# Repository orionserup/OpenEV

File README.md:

# OpenEV

A completely open source project designing electric vehicles from scratch.

All PCBs are made in [KiCad](https://www.kicad.org/) Version 6.0

All 3D Models are generated in [FreeCAD](https://www.freecadweb.org/) Version 0.19.1

All Firmware written in C using the [ESP-IDF](https://www.espressif.com/en/products/sdks/esp-idf) Framework

All Microcontrollers are using the Open Source [RISC-V](https://riscv.org/) Architecture: [ESP32-C3](https://www.espressif.com/en/products/socs/esp32-c3)

## Branches

* Sk8: Configuration for an Electric Skateboard
* Scoot: Configuration for Electric Scooters and Bikes

## Documentation

For each component there is a Documentation folder. For the Firmware components there are both PDF and HTML reference manuals. For the Hardware and Model Components there are PDF Data and Reference Sheets

## Authors

[Orion Serup](orionserup@gmail.com)

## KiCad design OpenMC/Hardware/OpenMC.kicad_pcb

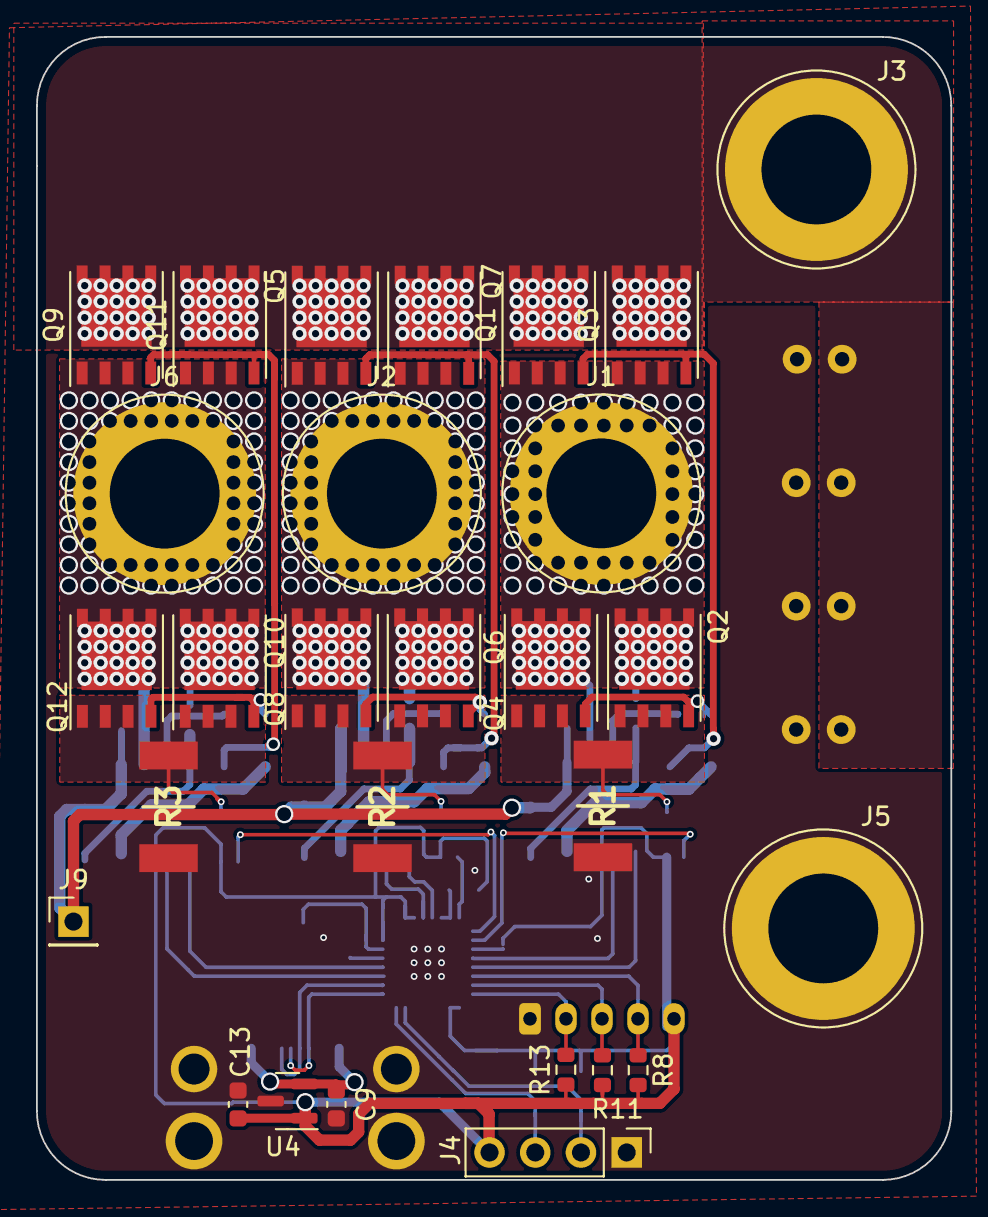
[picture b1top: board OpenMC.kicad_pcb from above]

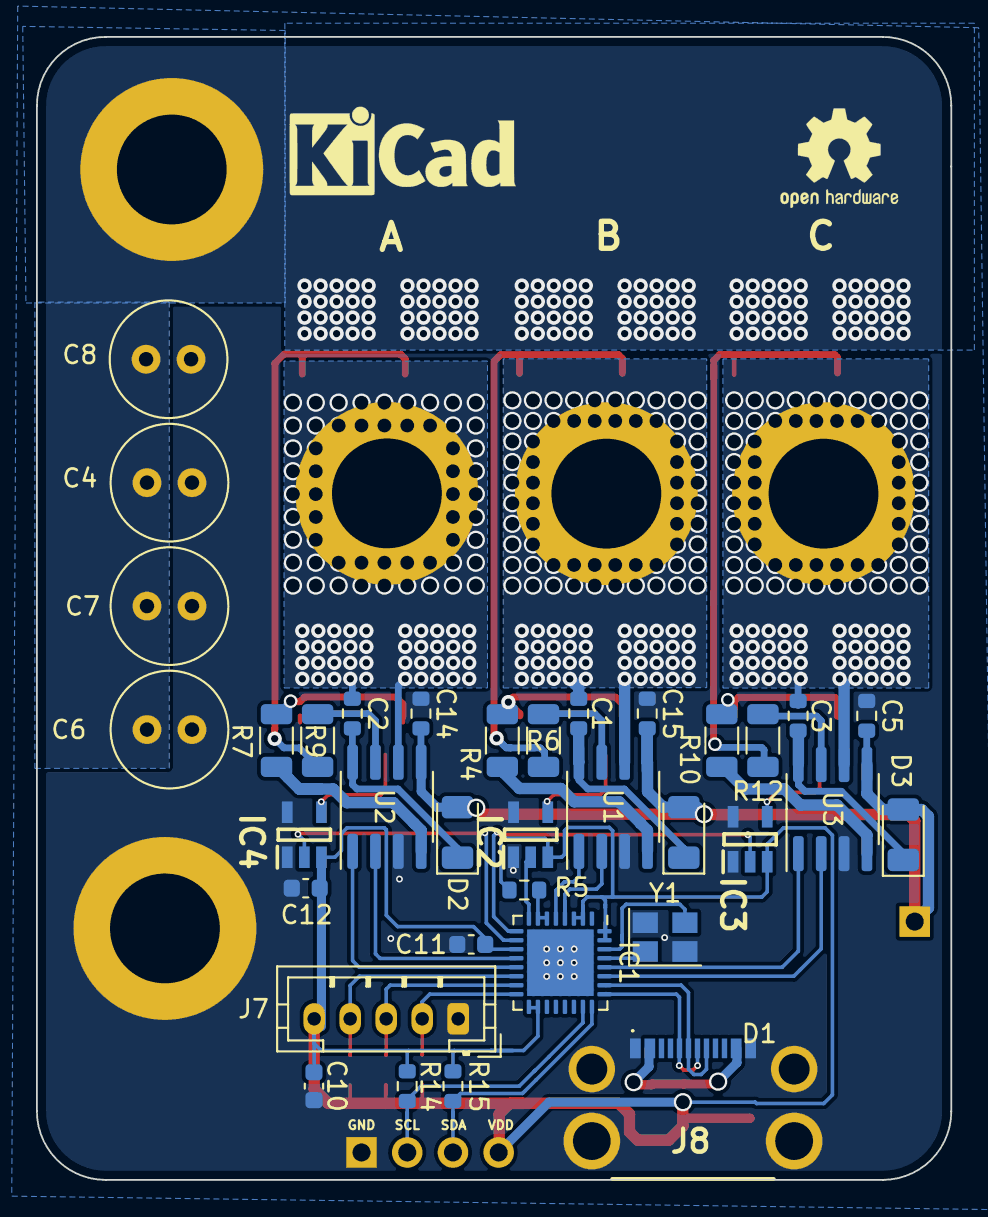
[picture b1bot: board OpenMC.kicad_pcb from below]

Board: 2 copper layers, 50.8 x 63.5 mm, 63 parts (35 on the bottom side), 45 nets.

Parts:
C1, C2, C3, C5, C14, C15: 1uF; R_0603_1608Metric
C4, C6, C7, C8: 27uF; C_Radial_D6.3mm_H7.0mm_P2.50mm
C9, C10, C11, C12, C13: 1uF; C_0603_1608Metric
D1, D2, D3: D; D_1206_3216Metric
IC1: ESP32-C3; QFN-32-1EP_5x5mm_P0.5mm_EP3.7x3.7mm
IC2, IC3, IC4: INA186A4QDBVRQ1; SOT95P280X145-5N
J1, J2, J6: Conn_01x01_Female; Banana_Jack_1Pin
J3: Power+; Banana_Jack_1Pin
J4: Comm; PinHeader_1x04_P2.54mm_Vertical
J5: Power-; Banana_Jack_1Pin
J7: Hall Connector; JST_PH_B5B-PH-K_1x05_P2.00mm_Vertical
J8: 216990-0001; 2169900001
J9: Gate Drive Voltage; PinHeader_1x01_P2.54mm_Vertical
Q1, Q2, Q3, Q4, Q5, Q6, Q7, Q8, Q9, Q10, Q11, Q12: SIR188DP; PowerPAK_SO-8_Single
R1, R2, R3: WSLF25121L000FEB; RESC6430X38N
R4, R6, R7, R9, R10, R12: 10; R_1206_3216Metric
R5, R8, R11, R13, R14, R15: R_US; R_0603_1608Metric
U1, U2, U3: LT2190NTR; SOIC-8_3.9x4.9mm_P1.27mm
U4: LM3480-3.3; SOT-23
Y1: 40MHz; Crystal_SMD_SeikoEpson_TSX3225-4Pin_3.2x2.5mm

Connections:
+BATT: C4.1, C6.1, C7.1, C8.1, J3.1, Q1.5 (D), Q3.5 (D), Q5.5 (D), Q7.5 (D), Q9.5 (D), Q11.5 (D)
/A: C2.2, J1.1, Q1.1 (S), Q1.2 (S), Q1.3 (S), Q2.5 (D), Q3.1 (S), Q3.2 (S), Q3.3 (S), Q4.5 (D), U2.6 (V_{s})
/B: C1.2, J2.1, Q5.1 (S), Q5.2 (S), Q5.3 (S), Q6.5 (D), Q7.1 (S), Q7.2 (S), Q7.3 (S), Q8.5 (D), U1.6 (V_{s})
/C: C3.2, J6.1, Q9.1 (S), Q9.2 (S), Q9.3 (S), Q10.5 (D), Q11.1 (S), Q11.2 (S), Q11.3 (S), Q12.5 (D), U3.6 (V_{s})
/Controller/AH: IC1.13 (MTDO), U2.1 (H_{in})
/Controller/AL: IC1.12 (MTCK), U2.2 (L_{in})
/Controller/BH: IC1.5 (XTAL_32K_N), U1.1 (H_{in})
/Controller/BL: IC1.4 (XTAL_32K_P), U1.2 (L_{in})
/Controller/CH: IC1.28 (U0TXD), U3.1 (H_{in})
/Controller/CL: IC1.27 (U0RXD), U3.2 (L_{in})
/Controller/D+: IC1.26 (GPIO19), J8.A6 (DP1), J8.B6 (DP2)
/Controller/D-: IC1.25 (GPIO18), J8.A7 (DN1), J8.B7 (DN2)
/Controller/HALL_A: IC1.16 (GPIO10), J7.2, R13.2
/Controller/HALL_B: IC1.15 (GPIO9), J7.3, R11.2
/Controller/HALL_C: IC1.14 (GPIO8), J7.4, R8.2
/Controller/I_{SENSE}A: IC1.10 (MTDI), IC4.2 (OUT)
/Controller/I_{SENSE}B: IC1.8 (GPIO3), IC2.2 (OUT)
/Controller/I_{SENSE}C: IC1.9 (MTMS), IC3.2 (OUT)
/Controller/RST: IC1.6 (GPIO2), IC1.7 (CHIP_EN), R5.2
/Controller/SCL: IC1.23 (SPID), J4.2, R14.2
/Controller/SDA: IC1.24 (SPIQ), J4.3, R15.2
/Controller/VBUS: C9.1, J8.A4 (VBUS_1), J8.A9 (VBUS_2), J8.B4 (VBUS_3), J8.B9 (VBUS_4), U4.2 (VI)
/Driver FETs/AH: Q1.4 (G), Q3.4 (G), R9.2
/Driver FETs/AL: Q2.4 (G), Q4.4 (G), R7.1
/Driver FETs/BH: Q5.4 (G), Q7.4 (G), R6.2
/Driver FETs/BL: Q6.4 (G), Q8.4 (G), R4.1
/Driver FETs/CH: Q9.4 (G), Q11.4 (G), R12.2
/Driver FETs/CL: Q10.4 (G), Q12.4 (G), R10.1
/Driver FETs/ISA: IC4.4 (IN-), Q2.1 (S), Q2.2 (S), Q2.3 (S), Q4.1 (S), Q4.2 (S), Q4.3 (S), R1.2
/Driver FETs/ISB: IC2.4 (IN-), Q6.1 (S), Q6.2 (S), Q6.3 (S), Q8.1 (S), Q8.2 (S), Q8.3 (S), R2.2
/Driver FETs/ISC: IC3.4 (IN-), Q10.1 (S), Q10.2 (S), Q10.3 (S), Q12.1 (S), Q12.2 (S), Q12.3 (S), R3.2
/Pre-Driver/V_{DRIVE}: C5.1, C14.1, C15.1, D1.2 (A), D2.2 (A), D3.2 (A), J9.1, U1.5 (V_{cc}), U2.5 (V_{cc}), U3.5 (V_{cc})
/VDD: C10.1, C11.1, C12.1, C13.1, IC1.2 (VDD3P3_1), IC1.3 (VDD3P3_2), IC1.11 (VDD3P3_RTC), IC1.17 (VDD3P3_CPU), IC1.18 (VDD_SPI), IC1.31 (VDDA_1), IC1.32 (VDDA_2), IC2.3 (VS), IC3.3 (VS), IC4.3 (VS), J4.4, J7.5, R5.1, R8.1, R11.1, R13.1, R14.1, R15.1, U4.1 (VO)
Earth: C4.2, C5.2, C6.2, C7.2, C8.2, C9.2, C10.2, C11.2, C12.2, C13.2, C14.2, C15.2, IC1.33 (GND), IC2.1 (GND), IC2.5 (IN+), IC3.1 (GND), IC3.5 (IN+), IC4.1 (GND), IC4.5 (IN+), J4.1, J5.1, J7.1, J8.A1 (GND_1), J8.A12 (GND_2), J8.B1 (GND_3), J8.B12 (GND_4), J8.MH1, J8.MH2, J8.MH3, J8.MH4, R1.1, R2.1, R3.1, U1.3 (GND), U2.3 (GND), U3.3 (GND), U4.3 (GND), Y1.2, Y1.4
unnamed: C1.1, D1.1 (K), U1.8 (V_{B})
unnamed: C2.1, D2.1 (K), U2.8 (V_{B})
unnamed: C3.1, D3.1 (K), U3.8 (V_{B})
unnamed: IC1.29 (XTAL_N), Y1.1
unnamed: IC1.30 (XTAL_P), Y1.3
unnamed: R4.2, U1.4 (L_{out})
unnamed: R6.1, U1.7 (H_{out})
unnamed: R7.2, U2.4 (L_{out})
unnamed: R9.1, U2.7 (H_{out})
unnamed: R10.2, U3.4 (L_{out})
unnamed: R12.1, U3.7 (H_{out})

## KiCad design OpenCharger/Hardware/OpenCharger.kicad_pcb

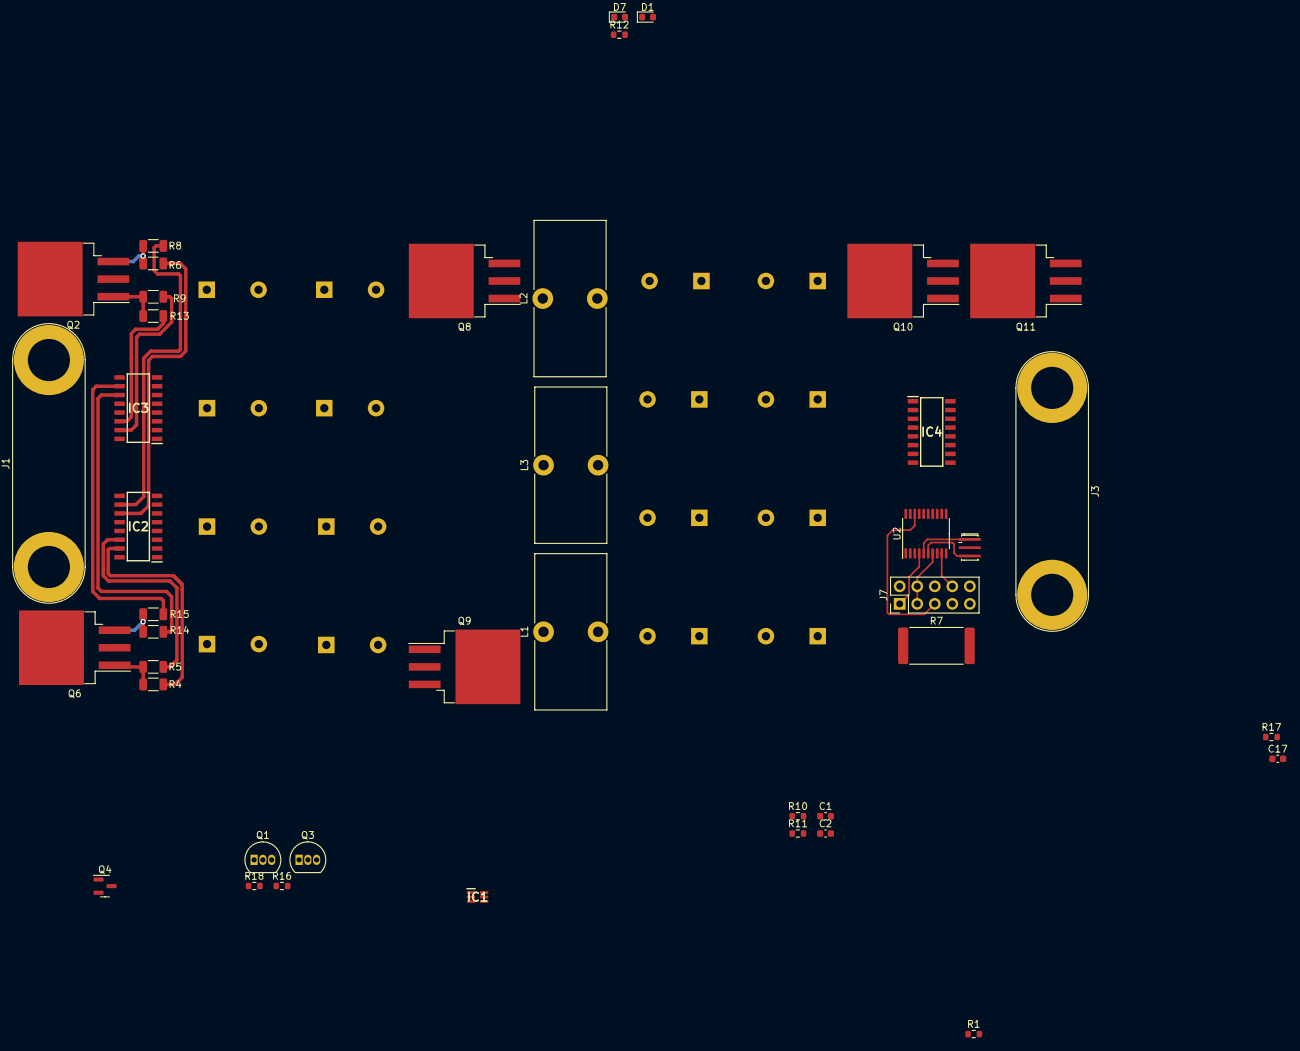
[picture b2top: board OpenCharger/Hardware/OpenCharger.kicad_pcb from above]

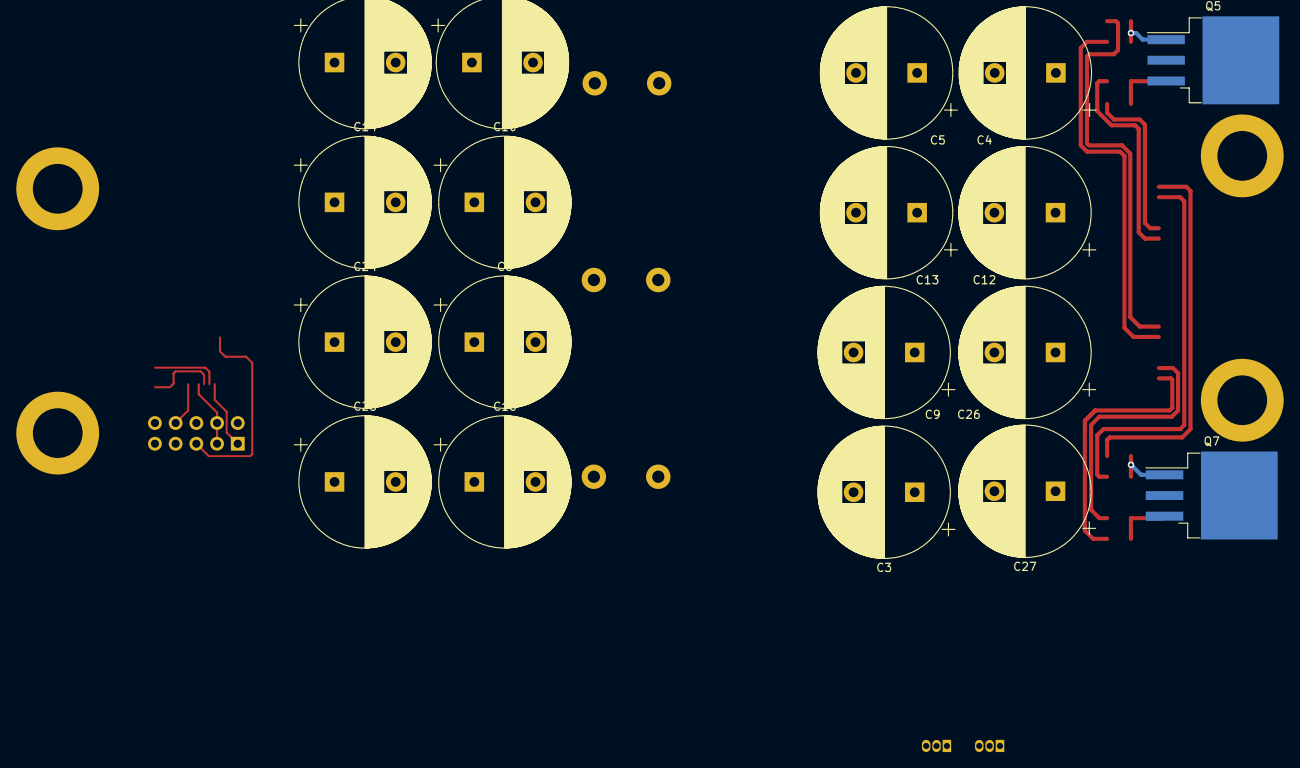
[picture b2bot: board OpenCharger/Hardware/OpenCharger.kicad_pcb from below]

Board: 2 copper layers, 60 parts (18 on the bottom side), 37 nets.

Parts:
C1, C2, C17: C; C_0603_1608Metric
C3, C4, C5, C6, C8, C9, C10, C12, C13, C14, C15, C16, C24, C25, C26, C27: 100uF; CP_Radial_D16.0mm_P7.50mm
D1, D7: 5V; D_0603_1608Metric
IC1: INA211CQDCKRQ1; SOT65P210X110-6N
IC2, IC3, IC4: STDRIVEG600TR; SOIC127P600X175-16N
J1, J3: Conn_01x02; Banana_Jack_2Pin
J7: Conn_02x05_Odd_Even; PinHeader_2x05_P2.54mm_Vertical
L1, L2, L3: L; L_Toroid_Vertical_L22.4mm_W10.2mm_P7.90mm_Vishay_TJ4
Q1, Q3: BS170; TO-92_Inline
Q2, Q5, Q6, Q7, Q8, Q9, Q10, Q11: Q_NMOS_GDS; TO-263-3_TabPin2
Q4: STB15N80K5; SOT-23
R1: 1k; R_0603_1608Metric
R4, R5, R6, R8, R9, R13, R14, R15: 10; R_1206_3216Metric
R7: .1m; R_4020_10251Metric
R10: 10k; R_0603_1608Metric
R11, R12, R16, R18: R_US; R_0603_1608Metric
R17: 99k; R_0603_1608Metric
U2: STM8AF6223A; TSSOP-20_4.4x6.5mm_P0.65mm
Y1: Resonator_Small; Resonator_SMD_Murata_CSTxExxV-3Pin_3.0x1.1mm_HandSoldering

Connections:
+3V3: IC1.3 (V+), J7.7, J7.8, R10.1, R16.1, R18.1, U2.9 (VDD)
+12V: IC2.2 (~SD/OD), IC2.4 (VCC), IC3.2 (~SD/OD), IC3.4 (VCC), IC4.2 (~SD/OD), IC4.4 (VCC)
/ChargeController/GND: C1.2, C3.2, C4.2, C5.2, C6.2, C8.2, C9.2, C10.2, C12.2, C13.2, C14.2, C15.2, C16.2, C17.2, C24.2, C25.2, C26.2, C27.2, D7.2 (A), IC1.1 (REF), IC1.2 (GND), IC2.9 (PGND), IC3.9 (PGND), IC4.9 (PGND), J7.3, J7.4, Q5.3 (S), Q7.3 (S), Q9.3 (S), R7.1, R12.2, U2.7 (VSS), Y1.2
/ChargeController/I_{BATT}_Sense: IC1.6 (OUT), U2.19 (PD2)
/ChargeController/SWIM: J7.5, U2.18 (PD1)
/ChargeController/SWITCH: IC4.1 (LIN), Q4.1 (G), U2.1 (PD4)
/ChargeController/V_{BATT}_Sense: C2.1, D1.1 (K), R1.1, R17.2, U2.20 (PD3)
/ChargeController/V_{in}_Sense: C1.1, D7.1 (K), R11.2, R12.1, U2.14 (PC4)
/ChargeController/~RST: J7.1, R10.2, U2.4 (NRST)
/DC-DC Converter/L+: IC4.13 (OUT), L1.1, L2.1, L3.1, Q8.3 (S), Q9.2 (D)
/DC-DC Converter/~SWITCH: IC4.3 (HIN), Q4.2 (D)
/FilteredRectifier/DGND: IC2.7 (SGND), IC3.7 (SGND)
/FilteredRectifier/NEG_ON: IC2.1 (LIN), IC3.3 (HIN), Q3.1 (D), R18.2
/FilteredRectifier/NHG: Q6.1 (G), R4.1, R5.1
/FilteredRectifier/NLG: Q7.1 (G), R14.1, R15.1
/FilteredRectifier/PHG: Q2.1 (G), R9.1, R13.1
/FilteredRectifier/PLG: Q5.1 (G), R6.1, R8.1
/FilteredRectifier/POS_ON: IC2.3 (HIN), IC3.1 (LIN), Q1.1 (D), Q3.2 (G), R16.2
/L1: IC2.13 (OUT), IC3.13 (OUT), J1.2, Q2.3 (S), Q5.2 (D)
/N: J1.1, Q6.3 (S), Q7.2 (D)
/V_{BATT}: IC1.5 (IN-), J3.1, Q11.2 (D), R17.1
/V_{DC}: C3.1, C4.1, C5.1, C9.1, C12.1, C13.1, C26.1, C27.1, Q2.2 (D), Q6.2 (D), Q8.2 (D)
/V_{REG}: C6.1, C8.1, C10.1, C14.1, C15.1, C16.1, C24.1, C25.1, L1.2, L2.2, L3.2, Q10.2 (D), R11.1
Earth: C2.2, D1.2 (A), IC4.7 (SGND), J3.2, Q4.3 (S), R1.2, R7.2
unnamed: C17.1, U2.8 (VCAP)
unnamed: IC2.10 (LOFF), R8.2
unnamed: IC2.11 (LON), R6.2
unnamed: IC2.14 (HOFF), R5.2
unnamed: IC2.15 (HON), R4.2
unnamed: IC3.10 (LOFF), R15.2
unnamed: IC3.11 (LON), R14.2
unnamed: IC3.14 (HOFF), R13.2
unnamed: IC3.15 (HON), R9.2
unnamed: Q1.3 (S), Q3.3 (S)
unnamed: Q10.3 (S), Q11.3 (S)
unnamed: U2.5 (PA1), Y1.1
unnamed: U2.6 (PA2), Y1.3

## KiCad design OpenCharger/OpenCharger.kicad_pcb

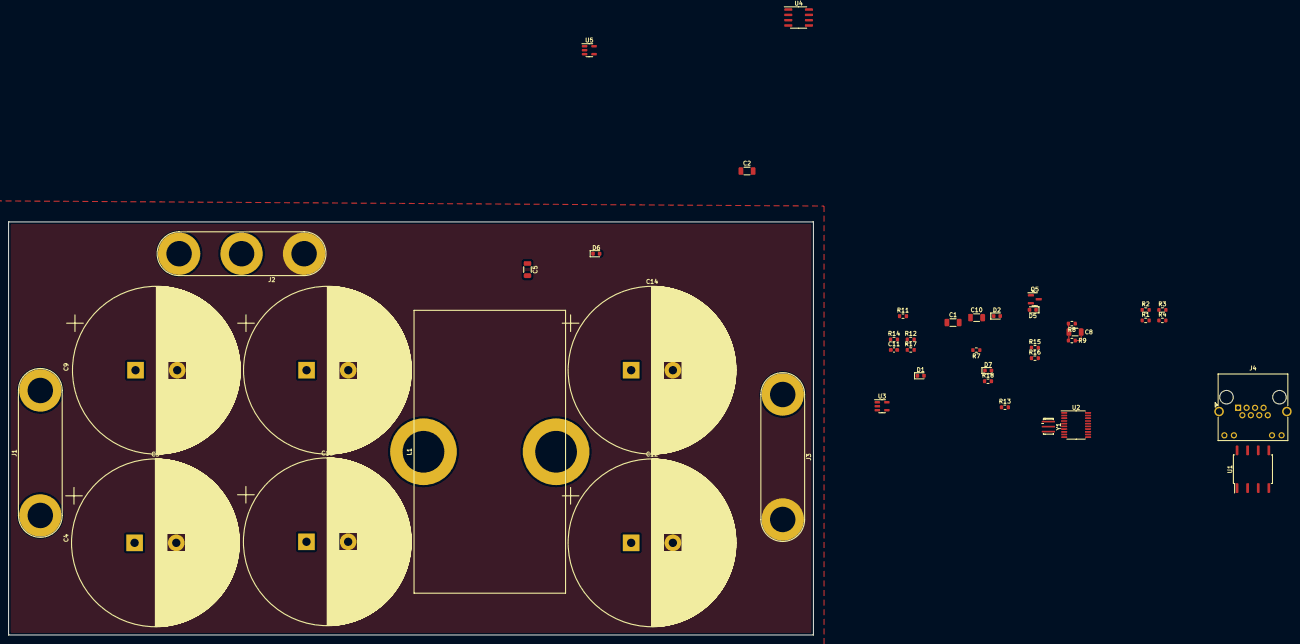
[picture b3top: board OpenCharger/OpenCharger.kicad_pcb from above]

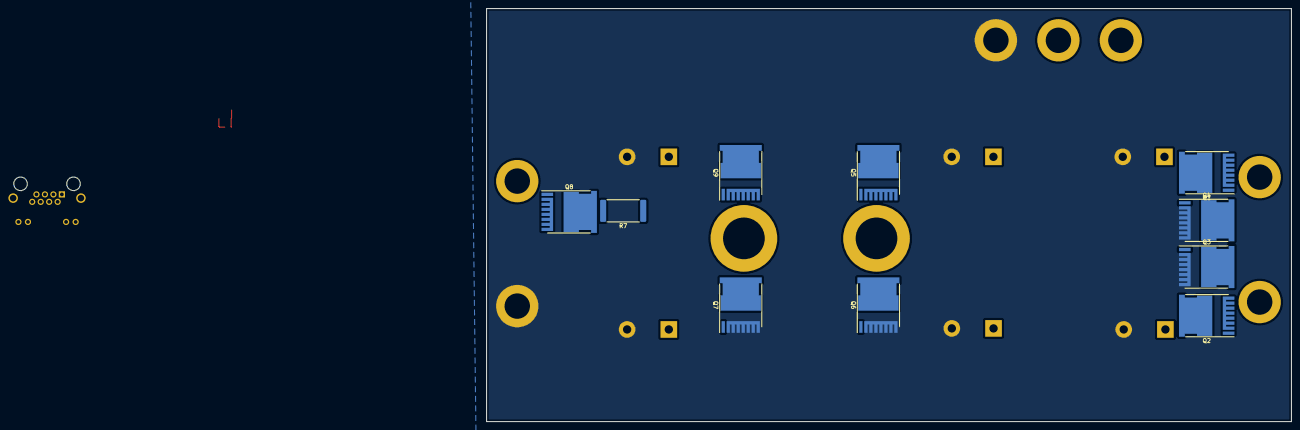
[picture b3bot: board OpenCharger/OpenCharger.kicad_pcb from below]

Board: 2 copper layers, 193.0 x 99.1 mm, 54 parts (10 on the bottom side), 31 nets.

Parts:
C1, C2, C5, C8, C10: C; C_1206_3216Metric
C3, C4, C9, C12, C13, C14: 56uF; CP_Radial_D40.0mm_P10.00mm_SnapIn
C11: C_Small; C_0603_1608Metric
D1, D2, D5, D6: 15V; D_0603_1608Metric
D7: 5V; D_0603_1608Metric
J1, J3: Conn_01x02; Banana_Jack_2Pin
J2: Conn_01x03; Banana_Jack_3Pin
J4: RJ45_LED; RJ45_Amphenol_RJHSE538X
L1: L; L_Toroid_Vertical_L67.6mm_W36.1mm_P31.80mm_Vishay_TJ9
Q1, Q2, Q3, Q4, Q5#2, Q6, Q7, Q8, Q9: IPT015N10N5; Infineon_PG-HSOF-8-1
Q5: BS870; SOT-23
R1, R2, R3, R4, R8: 20k; R_0603_1608Metric
R7, R9: 200k; R_0603_1608Metric
R7#2: R_Small; R_4020_10251Metric
R11, R12, R13, R14, R15, R16, R17, R18: R_US; R_0603_1608Metric
U1: ISO1050DUB; SOP-8_6.62x9.15mm_P2.54mm
U2: STM8AF6223A; TSSOP-20_4.4x6.5mm_P0.65mm
U3, U5: LMH6609MF; SOT-23-5
U4: IRS25606S; SOIC-8_3.9x4.9mm_P1.27mm
Y1: Resonator_Small; Resonator_SMD_Murata_CSTxExxV-3Pin_3.0x1.1mm_HandSoldering

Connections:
/CAN Transiever/CAN_GND: J4.6, U1.5 (GND2)
/CAN Transiever/CAN_H: J4.4, U1.7 (CANH)
/CAN Transiever/CAN_L: J4.5, U1.6 (CANL)
/CAN Transiever/CAN_VCC: J4.3, U1.8 (VCC2)
/CAN Transiever/GND: J4.9, J4.11, U1.4 (GND1)
/ChargeController/Buck_CTL: Q5.1 (G), U2.15 (PC5)
/ChargeController/V_{in}-: C8.2, R9.2
/ChargeController/V_{in}_Sense: D7.1 (K), R11.2, R12.1, U2.14 (PC4)
/DC-DC Converter/V_{in}-: D5.2 (A), Q5.2 (S)
/L1: C2.1, C5.2, J1.2, Q1.2 (S), Q4.3 (D), R2.1, R3.2
/N: C1.2, C10.1, J1.1, Q2.2 (S), Q3.3 (D), R1.2, R4.1
/V_{BATT}: J3.1, Q8.2 (S), R17.1
/V_{DC}: C3.1, C4.1, C9.1, C13.1, D1.1 (K), D2.1 (K), D6.2 (A), Q1.3 (D), Q2.3 (D), Q5#2.3 (D), R7.1, R8.1
/V_{REG}: C12.1, C14.1, Q9.3 (D), R7#2.1, R14.1
Earth: C3.2, C4.2, C9.2, C12.2, C13.2, C14.2, D7.2 (A), J2.1, J3.2, Q3.2 (S), Q4.2 (S), Q6.2 (S), Q7.2 (S), R12.2, R13.2, R18.2, U2.7 (VSS), Y1.2
unnamed: C1.1, D1.2 (A), Q1.1 (G), R1.1
unnamed: C2.2, D2.2 (A), Q2.1 (G), R2.2
unnamed: C5.1, Q3.1 (G), R3.1
unnamed: C8.1, D6.1 (K), R8.2, R9.1
unnamed: C10.2, Q4.1 (G), R4.2
unnamed: C11.1, R14.2, U3.3 (+)
unnamed: C11.2, R15.2, U3.4 (-)
unnamed: D5.1 (K), Q5.3 (D), R7.2
unnamed: L1.1, Q5#2.2 (S), Q6.3 (D)
unnamed: L1.2, Q7.3 (D), Q9.2 (S)
unnamed: Q8.3 (D), R7#2.2, R11.1, R15.1
unnamed: R16.1, U2.3 (PD6)
unnamed: R13.1, R16.2
unnamed: R17.2, R18.1, U5.3 (+)
unnamed: U2.5 (PA1), Y1.1
unnamed: U2.6 (PA2), Y1.3

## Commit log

2021-11-17 House Keeping and First Commit
2022-02-03 Updated Charger for Small
2022-02-04 Updated Charger and MC
2022-02-12 pcb work
2022-02-12 Updated structure
2022-02-15 Updated PCB
2022-02-17 updated mc
2022-02-17 update structure
2022-02-17 updated footprint
2022-03-02 chnage
